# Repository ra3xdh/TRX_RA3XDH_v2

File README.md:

## Описание

Схема и печатная плата для улучшенной версии моего трансивера из журнала Радио №2, 2009.

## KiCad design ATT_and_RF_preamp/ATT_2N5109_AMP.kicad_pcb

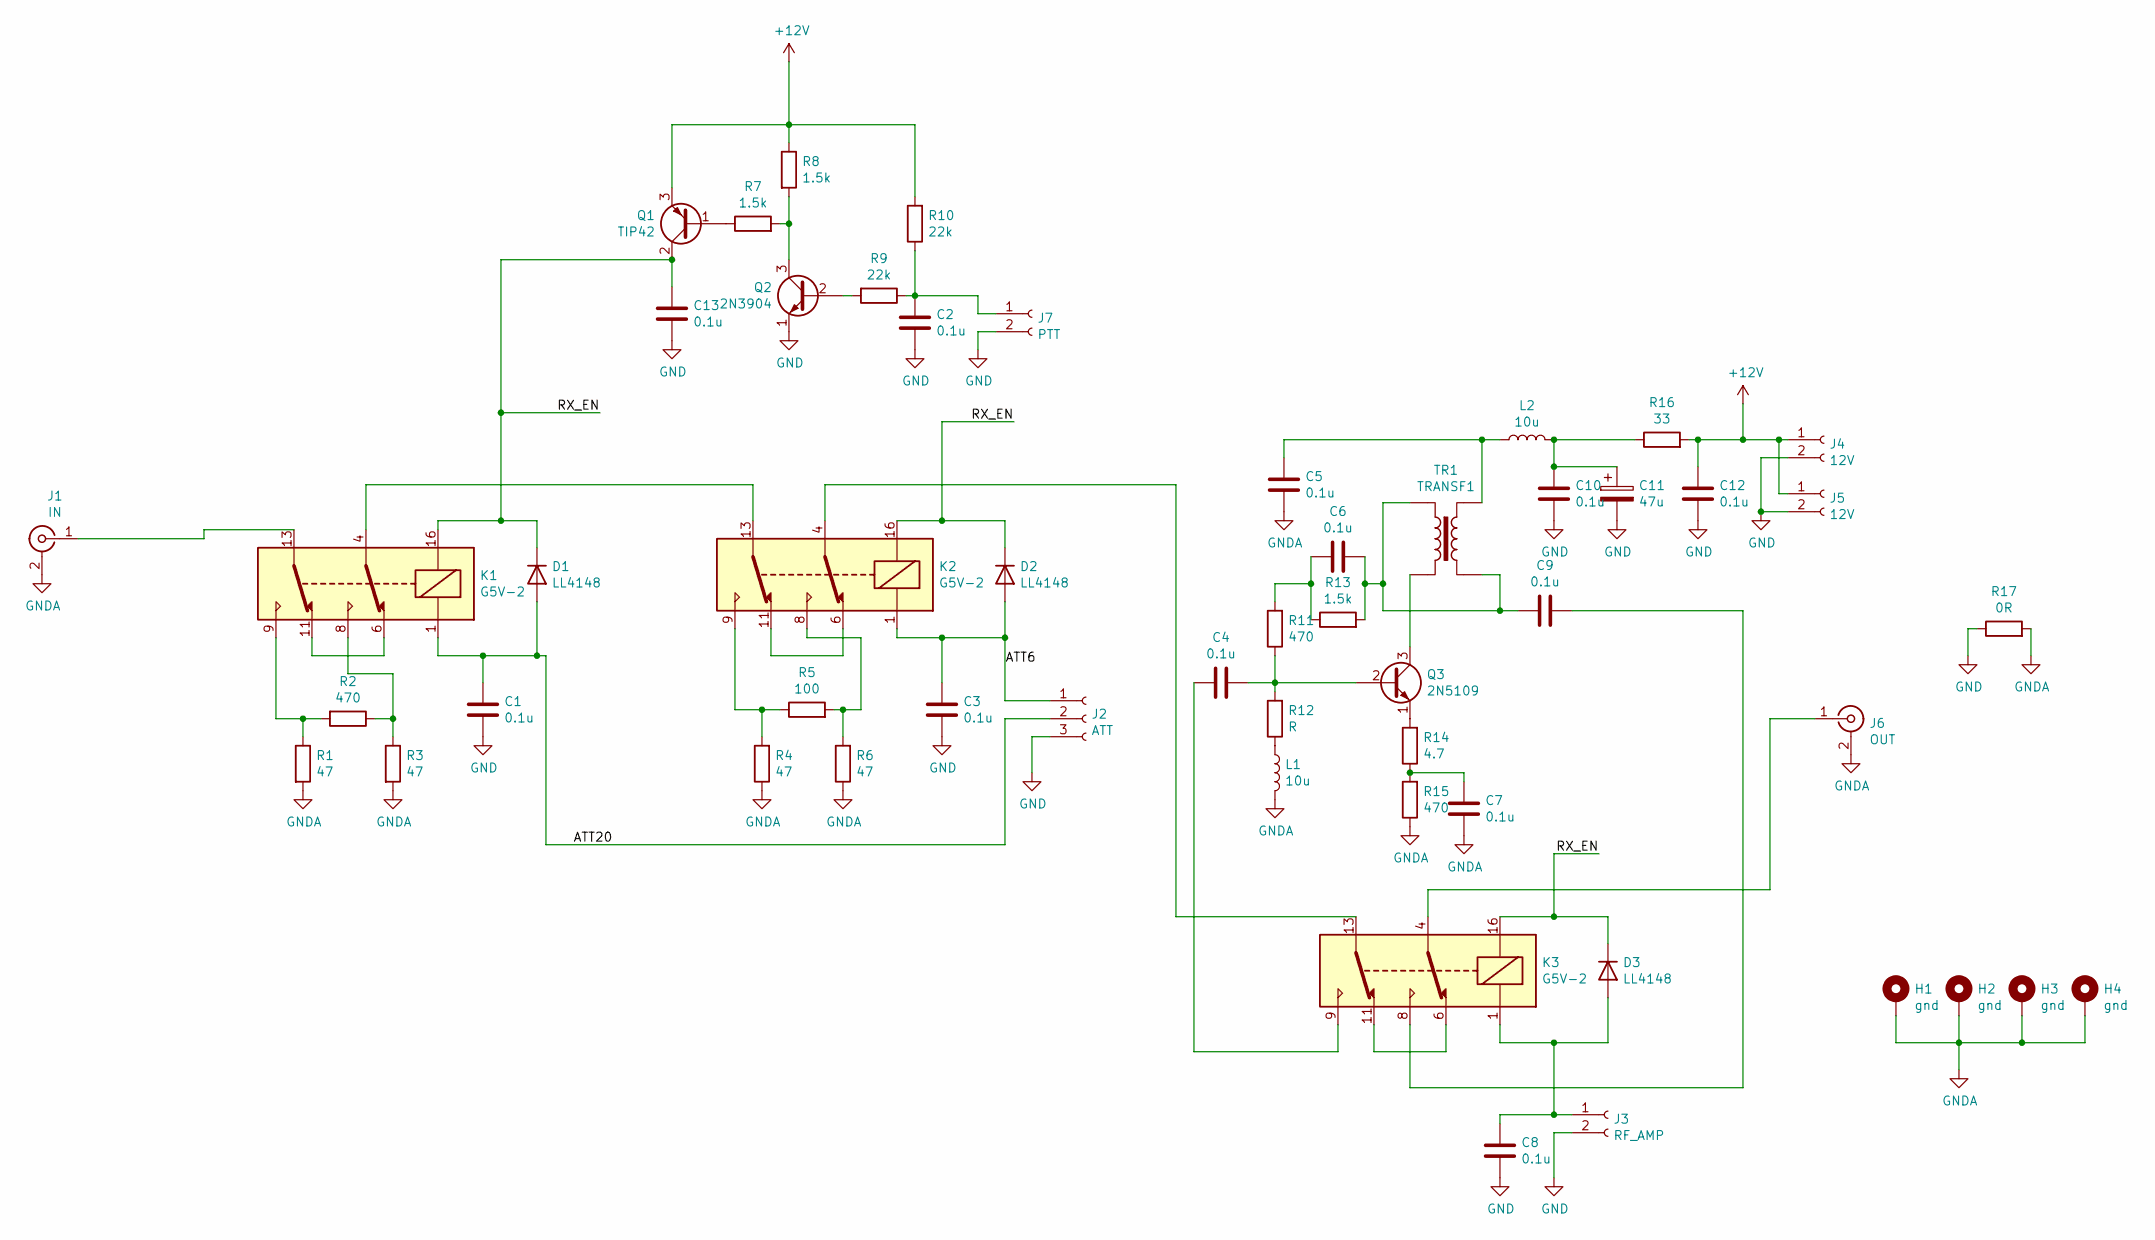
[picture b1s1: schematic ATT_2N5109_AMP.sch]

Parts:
C1, C2, C3, C4, C5, C6, C7, C8, C9, C10, C12, C13: 0.1u; C_0805_2012Metric_Pad1.18x1.45mm_HandSolder
C11: 47u; CP_Radial_D5.0mm_P2.50mm
D1, D2, D3: LL4148; D_MiniMELF
H1, H2, H3, H4: gnd; MountingHole_3.2mm_M3_ISO14580_Pad
J1: IN; SMA_Amphenol_132134_Vertical
J2: ATT; JST_EH_B3B-EH-A_1x03_P2.50mm_Vertical
J3: RF_AMP; JST_EH_B2B-EH-A_1x02_P2.50mm_Vertical
J4, J5: 12V; JST_EH_B2B-EH-A_1x02_P2.50mm_Vertical
J6: OUT; SMA_Amphenol_132134_Vertical
J7: PTT; JST_EH_B2B-EH-A_1x02_P2.50mm_Vertical
K1, K2, K3: G5V-2; Relay_DPDT_Omron_G5V-2
L1, L2: 10u; L2.5x6
Q1: TIP42; TO-220-3_Vertical
Q2: 2N3904; TO-92_Inline
Q3: 2N5109; TO-5-3
R1, R3, R4, R6: 47; R_0805_2012Metric_Pad1.20x1.40mm_HandSolder
R2, R11, R15: 470; R_0805_2012Metric_Pad1.20x1.40mm_HandSolder
R5: 100; R_0805_2012Metric_Pad1.20x1.40mm_HandSolder
R7, R8, R13: 1.5k; R_0805_2012Metric_Pad1.20x1.40mm_HandSolder
R9, R10: 22k; R_0805_2012Metric_Pad1.20x1.40mm_HandSolder
R12: R; R_0805_2012Metric_Pad1.20x1.40mm_HandSolder
R14: 4.7; R_0805_2012Metric_Pad1.20x1.40mm_HandSolder
R16: 33; R_0805_2012Metric_Pad1.20x1.40mm_HandSolder
R17: 0R; R_0805_2012Metric_Pad1.20x1.40mm_HandSolder
TR1: TRANSF1; L_Toroid_Vertical_L10.0mm_W5.0mm_4pin

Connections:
+12V: C12.1, J4.1, J5.1, Q1.3 (E), R8.1, R10.2, R16.2
/ATT6: C3.1, D2.2 (A), J2.1, K2.1
/ATT20: C1.1, D1.2 (A), J2.2, K1.1
/RX_EN: C13.1, D1.1 (K), D2.1 (K), D3.1 (K), K1.16, K2.16, K3.16, Q1.2 (C)
GND: C1.2, C2.2, C3.2, C8.2, C10.2, C11.2, C12.2, C13.2, J2.3, J3.2, J4.2, J5.2, J7.2, Q2.1 (E), R17.1
GNDA: C5.2, C7.2, H1.1, H2.1, H3.1, H4.1, J1.2 (Ext), J6.2 (Ext), L1.2, R1.2, R3.2, R4.1, R6.1, R15.1, R17.2
unnamed: C2.1, J7.1, R9.1, R10.1
unnamed: C4.1, Q3.2 (B), R11.1, R12.2
unnamed: C4.2, K3.9
unnamed: C5.1, L2.1, TR1.4
unnamed: C6.1, C9.2, R13.2, TR1.1, TR1.3
unnamed: C6.2, R11.2, R13.1
unnamed: C7.1, R14.1, R15.2
unnamed: C8.1, D3.2 (A), J3.1, K3.1
unnamed: C9.1, K3.8
unnamed: C10.1, C11.1, L2.2, R16.1
unnamed: J1.1 (In), K1.13
unnamed: J6.1 (In), K3.4
unnamed: K1.4, K2.13
unnamed: K1.8, R2.1, R3.1
unnamed: K1.9, R1.1, R2.2
unnamed: K1.6, K1.11
unnamed: K2.4, K3.13
unnamed: K2.8, R5.2, R6.2
unnamed: K2.9, R4.2, R5.1
unnamed: K2.6, K2.11
unnamed: K3.6, K3.11
unnamed: L1.1, R12.1
unnamed: Q1.1 (B), R7.1
unnamed: Q2.2 (B), R9.2
unnamed: Q2.3 (C), R7.2, R8.2
unnamed: Q3.1 (E), R14.2
unnamed: Q3.3 (C), TR1.2

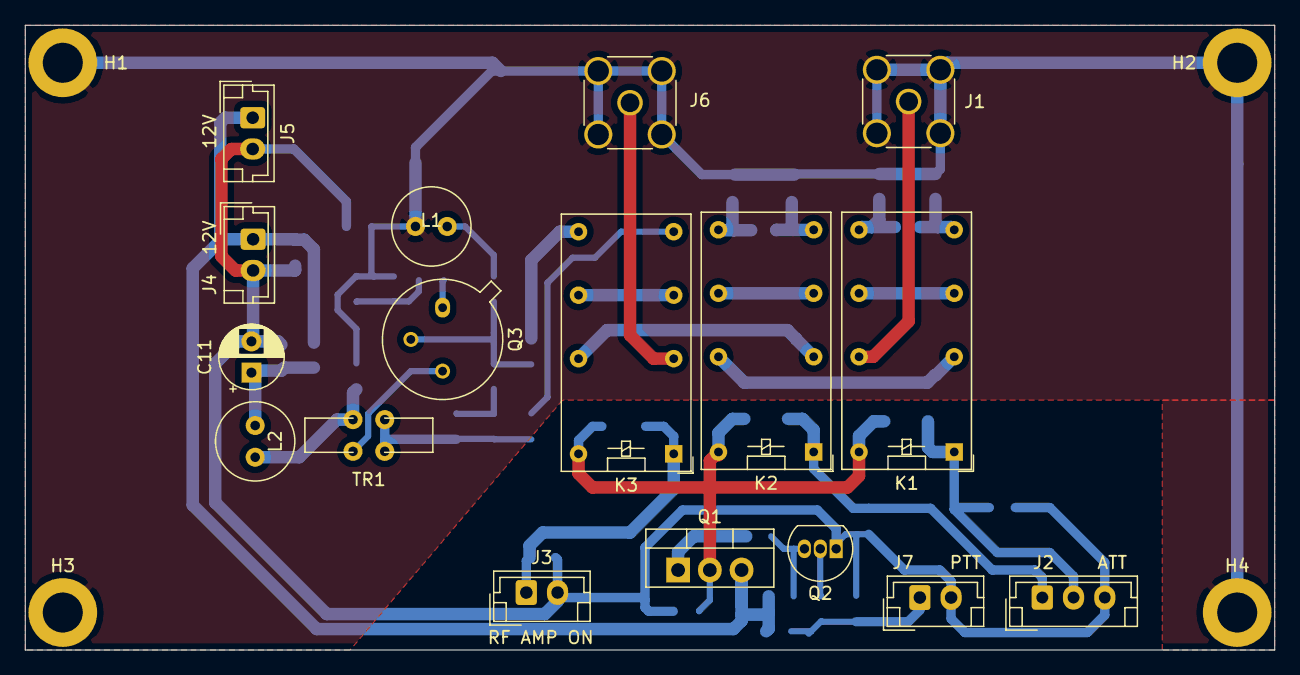
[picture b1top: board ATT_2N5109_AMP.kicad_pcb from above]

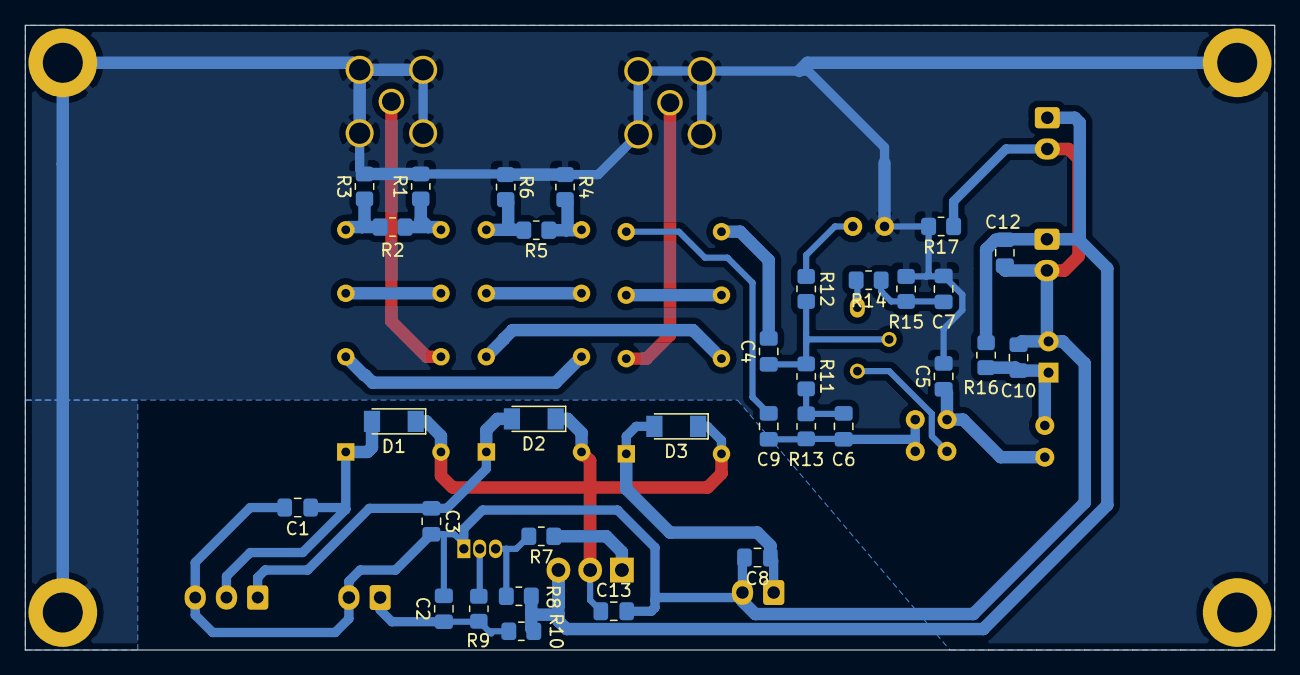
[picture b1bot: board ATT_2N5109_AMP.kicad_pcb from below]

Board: 2 copper layers, 100.0 x 50.0 mm, 53 parts (32 on the bottom side), 33 nets.

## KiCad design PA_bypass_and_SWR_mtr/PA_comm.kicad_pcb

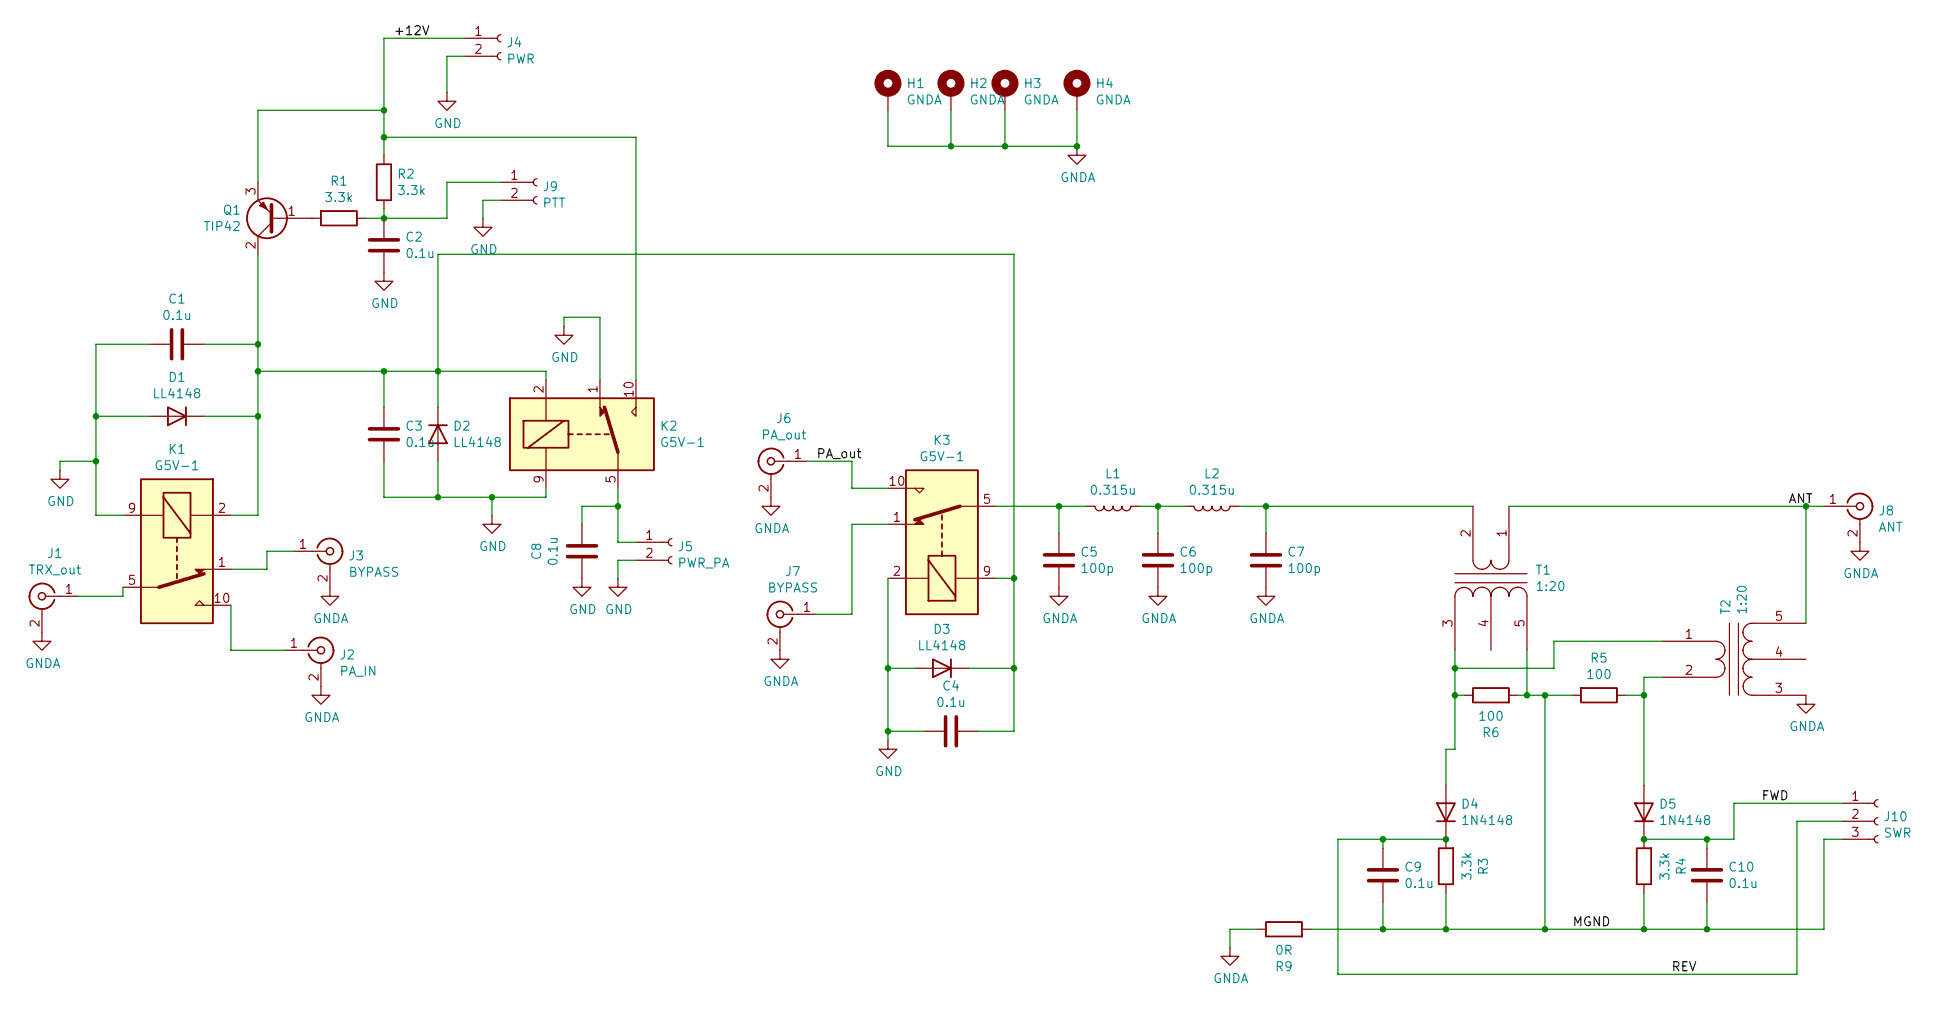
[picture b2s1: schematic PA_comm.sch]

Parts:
C1, C2, C3, C4, C8, C9, C10: 0.1u; C_0805_2012Metric
C5, C6, C7: 100p; C_Disc_D4.3mm_W1.9mm_P5.00mm
D1, D2, D3: LL4148; D_MiniMELF
D4, D5: 1N4148; D_DO-35_SOD27_P7.62mm_Horizontal
H1, H2, H3, H4: GNDA; MountingHole_3.2mm_M3_DIN965_Pad
J1: TRX_out; SMA_Amphenol_901-144_Vertical
J2: PA_IN; SMA_Amphenol_901-144_Vertical
J3, J7: BYPASS; SMA_Amphenol_901-144_Vertical
J4: PWR; JST_EH_B2B-EH-A_1x02_P2.50mm_Vertical
J5: PWR_PA; JST_EH_B2B-EH-A_1x02_P2.50mm_Vertical
J6: PA_out; SMA_Amphenol_901-144_Vertical
J8: ANT; SMA_Amphenol_901-144_Vertical
J9: PTT; JST_EH_B2B-EH-A_1x02_P2.50mm_Vertical
J10: SWR; JST_EH_B3B-EH-A_1x03_P2.50mm_Vertical
K1, K2, K3: G5V-1; Relay_SPDT_Omron_G5V-1
L1, L2: 0.315u; L_Toroid_Vertical_L10.0mm_W5.0mm_P5.08mm
Q1: TIP42; TO-220-3_Vertical
R1, R2, R3, R4: 3.3k; R_0805_2012Metric
R5, R6: 100; R_0805_2012Metric
R9: 0R; R_0805_2012Metric
T1, T2: 1:20; Current_transf_toroid_5x10mm

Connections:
/+12V: J4.1, K2.10, Q1.3 (E), R2.1
/ANT: J8.1 (In), T1.1 (AA), T2.5 (SB)
/FWD: C10.1, D5.1 (K), J10.1, R4.2
/MGND: C9.2, C10.2, J10.3, R3.1, R4.1, R5.2, R6.2, R9.2, T1.5 (SB)
/PA_out: J6.1 (In), K3.10
/REV: C9.1, D4.1 (K), J10.2, R3.2
GND: C1.2, C2.2, C3.2, C4.1, C8.1, D1.2 (A), D2.2 (A), D3.2 (A), J4.2, J5.2, J9.2, K1.9, K2.1, K2.9, K3.2
GNDA: C5.2, C6.2, C7.2, H1.1, H2.1, H3.1, H4.1, J1.2 (Ext), J2.2 (Ext), J3.2 (Ext), J6.2 (Ext), J7.2 (Ext), J8.2 (Ext), R9.1, T2.3 (SA)
unnamed: C1.1, C3.1, C4.2, D1.1 (K), D2.1 (K), D3.1 (K), K1.2, K2.2, K3.9, Q1.2 (C)
unnamed: C2.1, J9.1, R1.1, R2.2
unnamed: C5.1, K3.5, K3.6, L1.2
unnamed: C6.1, L1.1, L2.2
unnamed: C7.1, L2.1, T1.2 (AB)
unnamed: C8.2, J5.1, K2.5, K2.6
unnamed: D4.2 (A), R6.1, T1.3 (SA), T2.1 (AA)
unnamed: D5.2 (A), R5.1, T2.2 (AB)
unnamed: J1.1 (In), K1.5, K1.6
unnamed: J2.1 (In), K1.10
unnamed: J3.1 (In), K1.1
unnamed: J7.1 (In), K3.1
unnamed: Q1.1 (B), R1.2

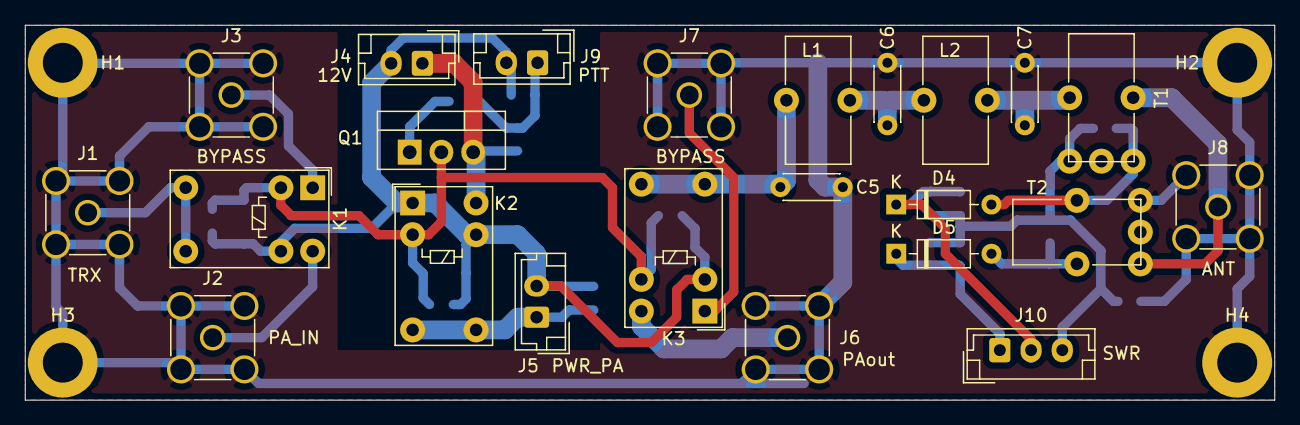
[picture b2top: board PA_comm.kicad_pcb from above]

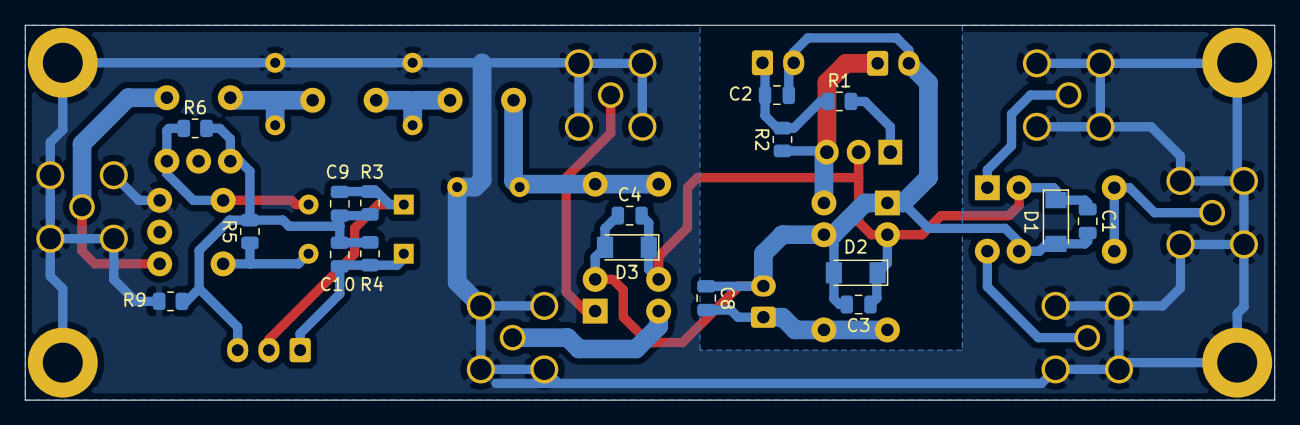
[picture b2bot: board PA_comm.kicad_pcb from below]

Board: 2 copper layers, 100.0 x 30.0 mm, 44 parts (17 on the bottom side), 21 nets.

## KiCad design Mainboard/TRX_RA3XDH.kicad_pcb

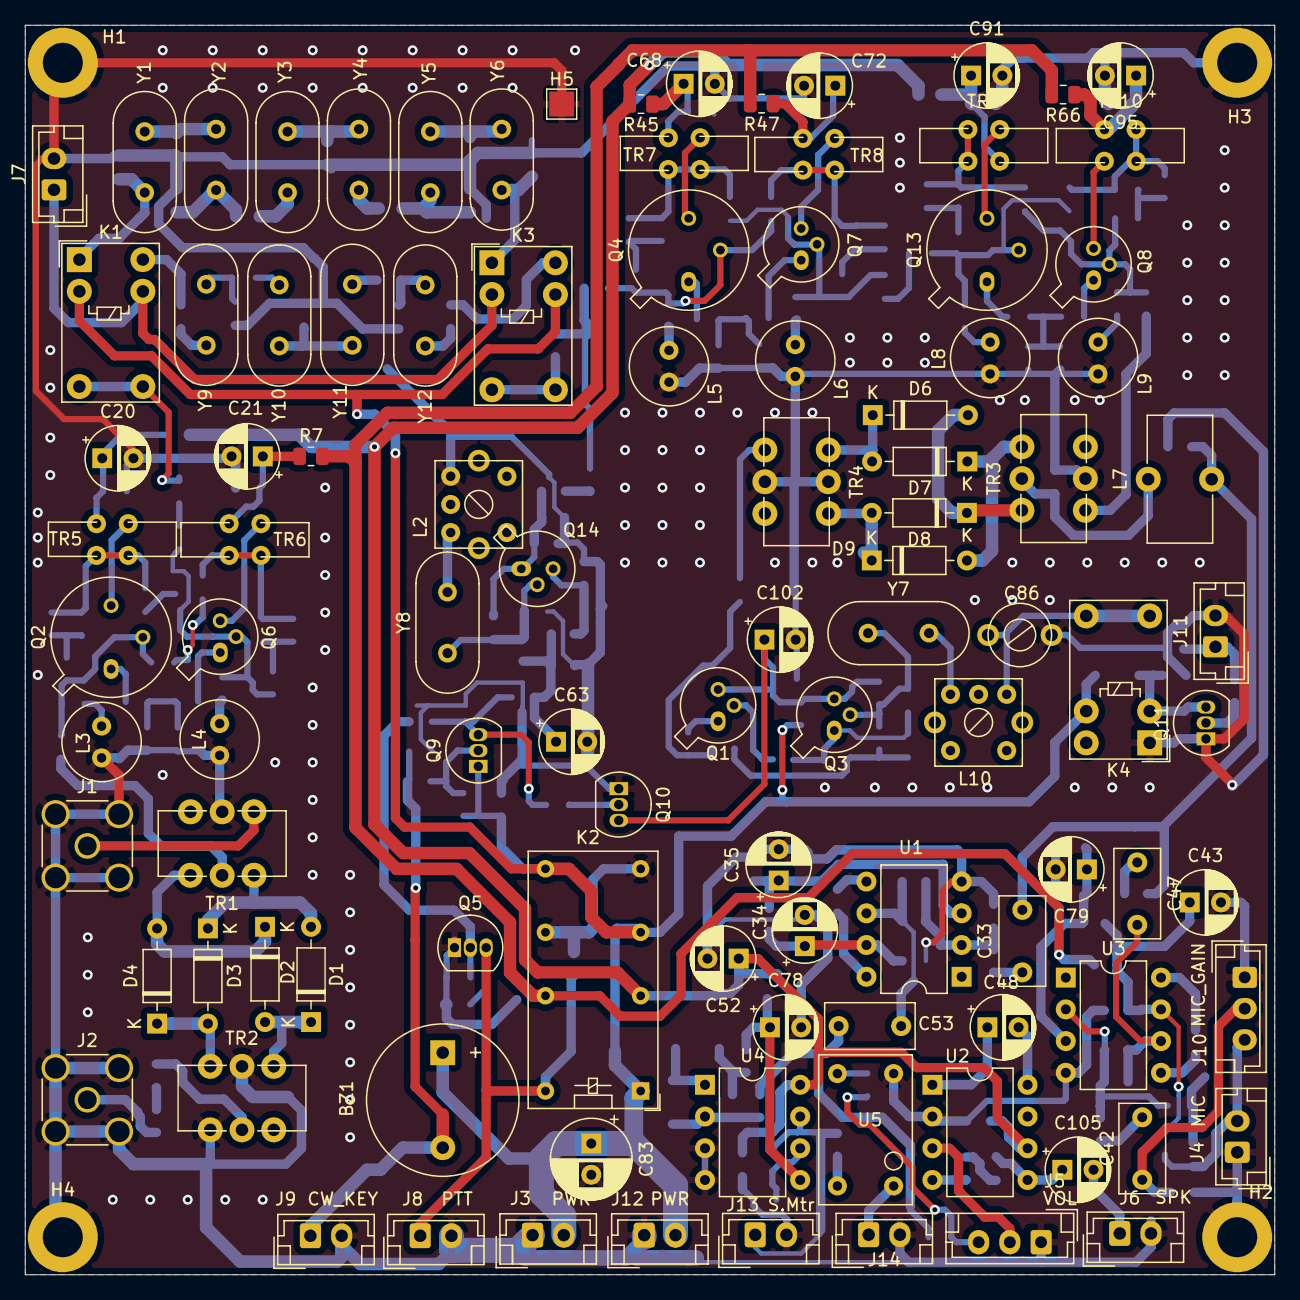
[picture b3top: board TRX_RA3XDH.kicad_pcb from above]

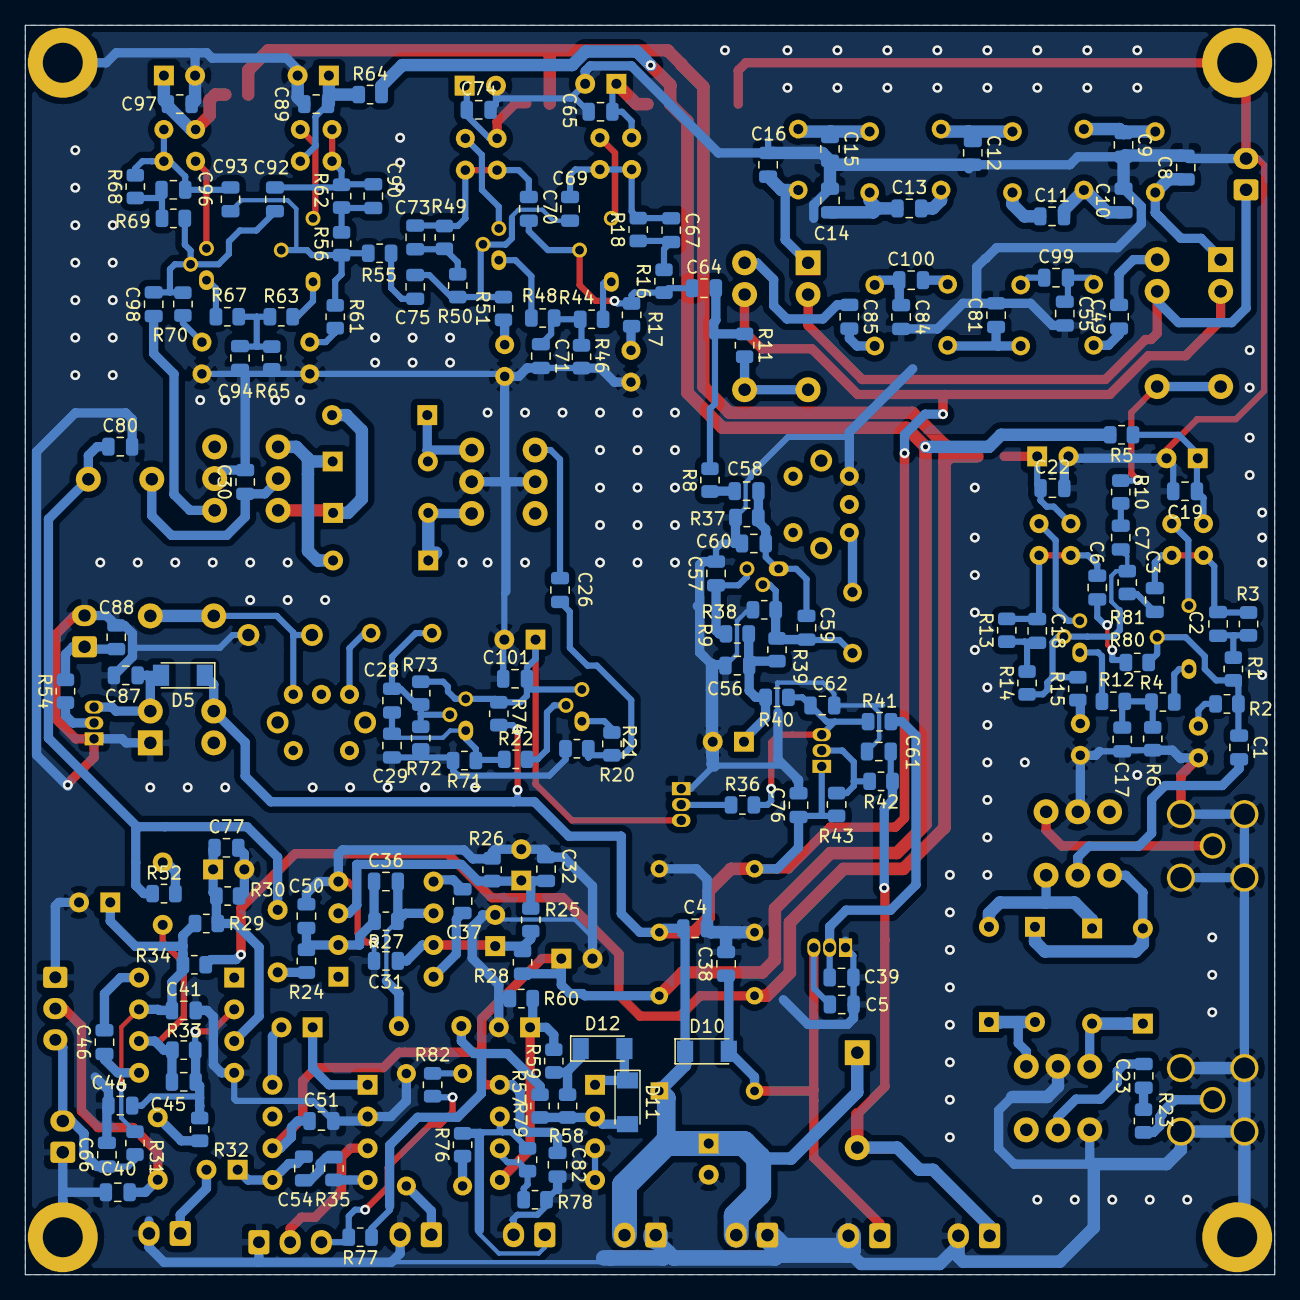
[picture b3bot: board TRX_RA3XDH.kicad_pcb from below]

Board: 2 copper layers, 100.0 x 100.0 mm, 264 parts (157 on the bottom side), 149 nets.

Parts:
BZ1: Buzzer; Buzzer_12x9.5RM7.6
C1, C3, C6, C7, C23, C26, C64, C69, C70, C92, C93: 10n; C_0805_2012Metric
C2, C4, C5, C17, C18, C19, C22, C31, C32, C38, C39, C41, C51, C54, C56, C57, C61, C62, C65, C67, C71, C73, C74, C75, C76, C77, C82, C87, C88, C89, C90, C94, C96, C97, C98, C101: 0.1u; C_0805_2012Metric
C8, C16: 39p; C_0805_2012Metric
C9, C10, C14, C15: 100p; C_0805_2012Metric
C11, C13: 330p; C_0805_2012Metric
C12: 120p; C_0805_2012Metric
C20, C21, C34, C35, C43, C48, C52, C63, C68, C72, C79, C91, C95, C102, C105: 10u; CP_Radial_D5.0mm_P2.50mm
C28, C29, C58, C59, C60: 22p; C_0805_2012Metric
C30, C40, C44, C50, C66, C80: 47n; C_0805_2012Metric
C33, C42, C47, C53: 1.0; C_Rect_L7.0mm_W3.5mm_P5.00mm
C36: 680p; C_0805_2012Metric
C37, C46: 33p; C_0805_2012Metric
C45: 1000p; C_0805_2012Metric
C49, C55, C84, C85: 240p; C_0805_2012Metric
C78: 1u; CP_Radial_D5.0mm_P2.50mm
C81: 390p; C_0805_2012Metric
C83: 100u; CP_Radial_D6.3mm_P2.50mm
C86: CTRIM; Ctrimm_5mm
C99, C100: 470p; C_0805_2012Metric
D1, D2, D3, D4, D6, D7, D8, D9: 1N5711; D_DO-35_SOD27_P7.62mm_Horizontal
D5, D10, D11, D12: LL4148; D_MiniMELF
H1, H2, H3, H4: GND; MountingHole_3.2mm_M3_DIN965_Pad
H5: gnd; TestPoint_Pad_2.0x2.0mm
J1: RF_INOUT; SMA_Amphenol_132291_Vertical
J2: VFO; SMA_Amphenol_132291_Vertical
J3, J12: PWR; JST_EH_B2B-EH-A_1x02_P2.50mm_Vertical
J4: MIC; JST_EH_B2B-EH-A_1x02_P2.50mm_Vertical
J5: VOL; JST_EH_B3B-EH-A_1x03_P2.50mm_Vertical
J6: SPK; JST_EH_B2B-EH-A_1x02_P2.50mm_Vertical
J7: CW_FLT; JST_EH_B2B-EH-A_1x02_P2.50mm_Vertical
J8: PTT; JST_EH_B2B-EH-A_1x02_P2.50mm_Vertical
J9: CW_KEY; JST_EH_B2B-EH-A_1x02_P2.50mm_Vertical
J10: MIC_GAIN; JST_EH_B3B-EH-A_1x03_P2.50mm_Vertical
J11: USB; JST_EH_B2B-EH-A_1x02_P2.50mm_Vertical
J13: S-Met.; JST_EH_B2B-EH-A_1x02_P2.50mm_Vertical
J14: AGC; JST_EH_B2B-EH-A_1x02_P2.50mm_Vertical
K1, K3, K4: G5V-1; Relay_SPDT_Omron_G5V-1
K2: G5V-2; Relay_DPDT_Omron_G5V-2
L2, L10: 3u; NEOSID_5t_4.5x4.5mm_132
L3, L4, L5, L6, L8, L9: 33u; L2.5x6
L7: 33u; L_Toroid_Vertical_L10.0mm_W5.0mm_P5.08mm
Q1, Q3, Q6, Q7, Q8, Q14: 2N2222; TO-18-3
Q2, Q4, Q13: 2N5109; TO-5-3
Q5, Q10, Q11: 2N3904; TO-92_Inline
Q9: 2N3906; TO-92_Inline
R1, R2, R14, R15, R16, R17, R51, R56, R61, R70: 470; R_0805_2012Metric
R3, R13, R18, R49, R62, R68: 2.2k; R_0805_2012Metric
R4, R12, R35, R44, R63: 4.7; R_0805_2012Metric
R5, R7, R8, R10, R11, R45, R47, R55, R64, R66: 47; R_0805_2012Metric
R6, R9, R20, R28, R34, R40, R46, R52, R59, R65, R74, R76: 100; R_0805_2012Metric
R21, R80, R81: 33*; R_0805_2012Metric
R22: 1.5k; R_0805_2012Metric
R23: 33; R_0805_2012Metric
R24, R32, R57, R82: 1k; R_0805_2012Metric
R25, R26, R29, R30, R31: 20k; R_0805_2012Metric
R27: 120k; R_0805_2012Metric
R33, R58: 33k; R_0805_2012Metric
R36, R41, R42, R43, R54: 22k; R_0805_2012Metric
R37, R71: 360; R_0805_2012Metric
R38, R72: 6.8k; R_0805_2012Metric
R39, R73: 13k; R_0805_2012Metric
R48, R67: 8.2; R_0805_2012Metric
R50, R69: 270; R_0805_2012Metric
R60: 470k; R_0805_2012Metric
R77: 2k; R_0805_2012Metric
R78: 10k*; R_0805_2012Metric
R79: 10k; R_0805_2012Metric
TR1, TR2, TR3, TR4: FT37-43; L_Toroid_Vertical_L10.0mm_W5.0mm_6pin
TR5, TR6, TR7, TR8, TR9, TR10: FT37-43; L_Toroid_Vertical_L10.0mm_W5.0mm_4pin
U1, U3: NE5534; DIP-8_W7.62mm
U2: LM386; DIP-8_W7.62mm
U4: LM358; DIP-8_W7.62mm
U5: LCR0202; lcr0202
Y1, Y2, Y3, Y4, Y5, Y6, Y9, Y10, Y11, Y12: 8Mhz; Crystal_HC49-U_Vertical
Y7, Y8: 8.867Mhz; Crystal_HC49-U_Vertical

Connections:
+12V: BZ1.1, C4.1, C76.1, C83.1, D5.1, D10.1, J3.2, J12.2, K1.2, K2.1, K2.6, K2.9, K3.9, K4.9, Q9.1, R43.2, R74.1
/+12V_BFO2: C62.1, Q9.3, R36.2, R40.2, R41.1
/+12V_RX: C51.1, C52.1, C82.1, K2.4, R5.2, R28.1, R45.2, R64.2, U2.6, U4.8
/+12V_TX: K2.13, R7.2, R34.1, R47.2, R66.2
/CW_KEY: BZ1.2, C61.1, J9.1, R42.1
/MIC_IN: C40.1, C42.2, J10.2
/PTT: C5.1, C38.1, D10.2, J8.1, K2.16, Q5.3
/TX: C39.1, Q5.2, R41.2
/VGND_RX: C32.1, C35.1, R25.2, R26.1, U1.3
/VGND_TX: C77.1, C79.1, R29.2, R30.1, U3.3
/VOL_IN: C53.1, R57.1, R77.1
/VOL_OUT: J5.2, U2.3
GND: C4.2, C5.2, C8.2, C9.2, C10.2, C12.2, C14.2, C15.2, C16.2, C17.2, C19.2, C20.2, C21.2, C22.2, C29.2, C30.2, C31.2, C32.2, C34.2, C35.2, C38.2, C39.2, C40.2, C41.2, C43.2, C44.2, C50.2, C51.2, C52.2, C55.2, C56.2, C57.2, C60.2, C61.2, C62.2, C63.2, C65.2, C66.2, C68.2, C71.2, C72.2, C74.2, C76.2, C77.2, C78.2, C79.2, C80.2, C81.2, C82.2, C83.2, C84.2, C86.2, C87.2, C88.2, C89.2, C91.2, C94.2, C95.2, C97.2, C101.2, C102.2, H1.1, H2.1, H3.1, H4.1, H5.1, J1.2, J2.2, J3.1, J4.1, J5.1, J6.2, J7.2, J8.2, J9.2, J10.1, J11.2, J12.1, J13.2, J14.2, K2.8, K2.11, K4.1, L2.2, L3.2, L4.2, L5.2, L6.2, L8.2, L9.2, Q5.1, Q10.1, Q11.1, R6.1, R20.2, R26.2, R30.2, R35.1, R37.2, R38.2, R46.1, R60.2, R65.1, R71.2, R72.2, R78.2, TR1.5, TR2.2, TR2.4, TR3.5, TR4.2, TR4.5, U1.4, U2.2, U2.4, U3.4, U4.3, U4.4, U5.3
unnamed: C1.1, Q2.2, R1.1, R2.2, R80.2
unnamed: C1.2, TR1.2
unnamed: C2.1, C3.2, R3.2, TR5.1, TR5.3
unnamed: C2.2, R1.2, R3.1
unnamed: C3.1, R81.2
unnamed: C6.2, R80.1
unnamed: C7.1, R10.2
unnamed: C7.2, Q6.2, R14.1, R15.2, R81.1
unnamed: C8.1, K1.1, Y1.1
unnamed: C9.1, Y1.2, Y2.1
unnamed: C10.1, C11.2, Y2.2
unnamed: C11.1, Y3.1
unnamed: C12.1, Y3.2, Y4.1
unnamed: C13.1, C14.1, Y5.1
unnamed: C13.2, Y4.2
unnamed: C15.1, Y5.2, Y6.1
unnamed: C16.1, K3.1, Y6.2
unnamed: C17.1, R4.1, R6.2, R12.1
unnamed: C6.1, C18.1, R13.2, TR6.2, TR6.4
unnamed: C18.2, R13.1, R14.2
unnamed: C19.1, C20.1, R5.1, TR5.4
unnamed: C21.1, C22.1, R7.1, TR6.1
unnamed: C23.1, R23.1
unnamed: C23.2, TR2.5
unnamed: C26.1, R20.1, R21.2
unnamed: C26.2, TR4.4
unnamed: C28.1, Q3.2, R72.1, R73.2, Y7.1
unnamed: C28.2, C29.1, Q3.1, R22.1, R71.1
unnamed: C30.1, L7.1, TR3.2
unnamed: C31.1, C34.1, R25.1, R28.2, U1.7
unnamed: C33.1, R24.2
unnamed: C33.2, C80.1, L7.2, R52.1
unnamed: C36.1, C50.1, R24.1, R27.2, U1.2
unnamed: C36.2, C53.2, R27.1, U1.6
unnamed: C37.1, U1.5
unnamed: C37.2, U1.8
unnamed: C41.1, C43.1, R29.1, R31.1, R34.2, U3.7
unnamed: C42.1, R32.2
unnamed: C44.1, C45.1, R32.1, R33.2, U3.2
unnamed: C45.2, C47.2, R33.1, U3.6
unnamed: C46.1, U3.5
unnamed: C46.2, U3.8
unnamed: C47.1, R52.2
unnamed: C48.1, U2.1
unnamed: C48.2, U2.8
unnamed: C49.1, Y9.1
unnamed: C49.2, K1.10
unnamed: C54.1, R35.2
unnamed: C55.1, C99.2, Y9.2
unnamed: C56.1, C63.1, R9.1, R39.1, R40.1
unnamed: C57.1, Q14.3, R9.2
unnamed: C58.1, C59.2, C60.1, Q14.1, R37.1
unnamed: C58.2, R8.1
unnamed: C59.1, Q14.2, R38.1, R39.2, Y8.1
unnamed: C64.1, C70.2, Q4.2, R16.1, R17.2
unnamed: C64.2, R8.2, R11.1
unnamed: C65.1, C68.1, R45.1, TR7.4
unnamed: C66.1, J4.2, J10.3, R31.2
unnamed: C67.1, C69.2, R18.2, TR7.1, TR7.3
unnamed: C67.2, R16.2, R18.1
unnamed: C69.1, C75.2, Q7.2, R50.1, R51.2
unnamed: C70.1, C73.1, R49.2, TR8.2, TR8.4
unnamed: C71.1, R44.1, R46.2, R48.1
unnamed: C72.1, C74.1, R47.1, TR8.1
unnamed: C73.2, R49.1, R50.2
unnamed: C75.1, R55.2
unnamed: C78.1, R59.2, R60.1, U4.5
unnamed: C81.1, Y10.2, Y11.1
unnamed: C85.1, K3.10
unnamed: C85.2, Y12.2
unnamed: C86.1, K4.5, K4.6, L10.2
unnamed: C87.1, D5.2, K4.2, Q11.3
unnamed: C88.1, J11.1, R54.2
unnamed: C89.1, C91.1, R64.1, TR9.4
unnamed: C90.1, C92.2, R62.2, TR9.1, TR9.3
unnamed: C90.2, R56.2, R62.1
unnamed: C92.1, C98.2, Q8.2, R69.1, R70.2
unnamed: C93.1, C96.1, R68.2, TR10.2, TR10.4
unnamed: C93.2, Q13.2, R55.1, R56.1, R61.2
unnamed: C94.1, R63.1, R65.2, R67.1
unnamed: C95.1, C97.1, R66.1, TR10.1
unnamed: C96.2, R68.1, R69.2
unnamed: C98.1, TR3.4
unnamed: C99.1, Y10.1
unnamed: C84.1, C100.1, Y12.1
unnamed: C100.2, Y11.2
unnamed: C101.1, C102.1, Q1.3, Q3.3, Q10.3, R73.1, R74.2
unnamed: C54.2, C105.1, U2.5
unnamed: C105.2, J6.1
unnamed: D1.1, D2.2, TR2.1
unnamed: D1.2, D3.1, TR1.3
unnamed: D2.1, D4.2, TR1.1
unnamed: D3.2, D4.1, TR2.3
unnamed: D6.1, D7.2, TR4.3
unnamed: D6.2, D8.1, TR3.3
unnamed: D7.1, D9.2, TR3.1
unnamed: D8.2, D9.1, TR4.1
unnamed: D11.1, D12.2, U4.1
unnamed: D11.2, R57.2, R58.1, U4.2
unnamed: D12.1, R58.2, R59.1
unnamed: J1.1, TR1.4
unnamed: J2.1, R23.2
unnamed: J5.3, R77.2, R82.2
unnamed: J7.1, K1.9, K3.2
unnamed: J13.1, R76.2, R79.2, U4.7
unnamed: J14.1, U5.2
unnamed: K1.5, K1.6, R10.1
unnamed: K3.5, K3.6, R11.2
unnamed: L2.1, Y8.2
unnamed: L3.1, R2.1
unnamed: L4.1, R15.1
unnamed: L5.1, R17.1
unnamed: L6.1, R51.1
unnamed: L8.1, R61.1
unnamed: L9.1, R70.1
unnamed: L10.1, Y7.2
unnamed: Q1.1, R21.1
unnamed: Q1.2, R22.2
unnamed: Q2.1, R4.2
unnamed: Q2.3, TR5.2
unnamed: Q4.1, R44.2
unnamed: Q4.3, TR7.2
unnamed: Q6.1, R12.2
unnamed: Q6.3, TR6.3
unnamed: Q7.1, R48.2
unnamed: Q7.3, TR8.3
unnamed: Q8.1, R67.2
unnamed: Q8.3, TR10.3
unnamed: Q9.2, R42.2, R43.1
unnamed: Q10.2, R36.1
unnamed: Q11.2, R54.1
unnamed: Q13.1, R63.2
unnamed: Q13.3, TR9.2
unnamed: R76.1, U5.1
unnamed: R78.1, R79.1, U4.6
unnamed: R82.1, U5.4
